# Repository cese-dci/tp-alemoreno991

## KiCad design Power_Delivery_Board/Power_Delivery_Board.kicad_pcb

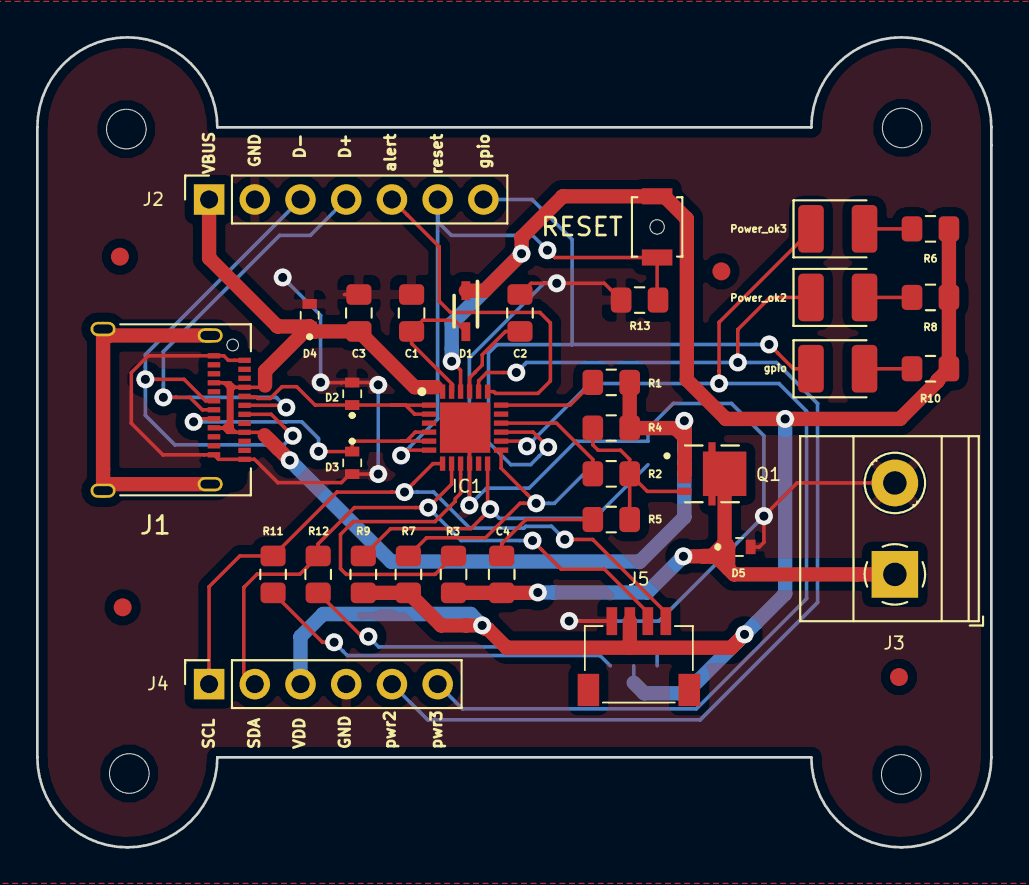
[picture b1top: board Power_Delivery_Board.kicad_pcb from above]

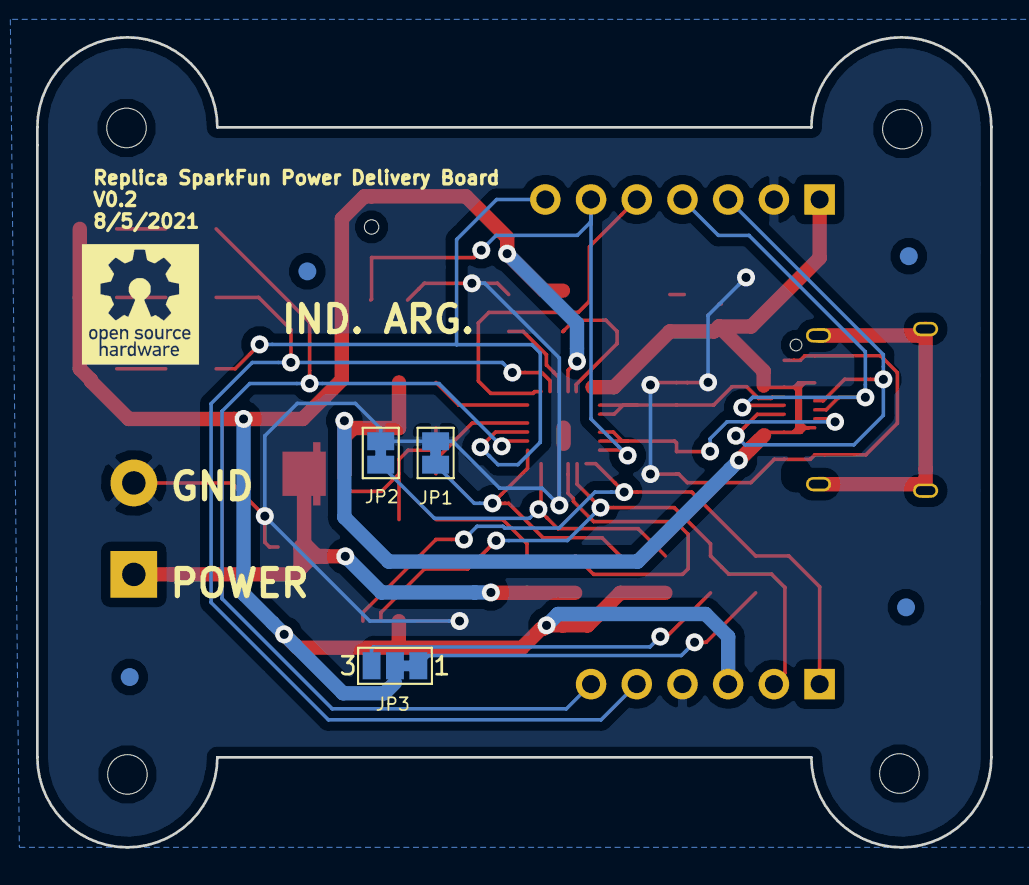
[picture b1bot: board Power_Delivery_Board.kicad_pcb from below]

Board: 2 copper layers, 53.0 x 45.0 mm, 36 parts (3 on the bottom side), 29 nets.

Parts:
C1, C2, C3: 1uF; C_0805_2012Metric_Pad1.15x1.40mm_HandSolder
C4: 0.1uF; C_0805_2012Metric_Pad1.15x1.40mm_HandSolder
D1: BAT60A; SOD2513X110N
D2, D3, D4, D5: 24V; ESDA8P801U1M
IC1: STUSB4500QTR; QFN50P400X400X100-25N-D
J1: USB C; USB_C_Receptacle_Amphenol_12401610E4-2A
J2: IO pins; PinSocket_1x07_P2.54mm_Vertical
J3: Power Output; TerminalBlock_Phoenix_MKDS-1,5-2-5.08_1x02_P5.08mm_Horizont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
J4: IO Pins; PinSocket_1x06_P2.54mm_Vertical
J5: Qwiic; 4208
JP1, JP2: solder_jumper; SolderJumper-2_P1.3mm_Bridged_Pad1.0x1.5mm
JP3: solder_jumper_triple; SolderJumper-3_P1.3mm_Bridged12_Pad1.0x1.5mm_NumberLabels
Power_ok2: amarillo; D_1210_3225Metric_Pad1.42x2.65mm_HandSolder
Power_ok3: azul; D_1210_3225Metric_Pad1.42x2.65mm_HandSolder
Q1: STL6P3LLH6; TRANS_STL6P3LLH6
R1, R3, R6, R8, R10: 1k; R_0805_2012Metric_Pad1.15x1.40mm_HandSolder
R2: 22k; R_0805_2012Metric_Pad1.15x1.40mm_HandSolder
R4, R7, R9, R13: 100k; R_0805_2012Metric_Pad1.15x1.40mm_HandSolder
R5: 100; R_0805_2012Metric_Pad1.15x1.40mm_HandSolder
R11, R12: 2k2; R_0805_2012Metric_Pad1.15x1.40mm_HandSolder
RESET: SW_Push; SW_SPST_B3U-1000P-B
gpio: verde; D_1210_3225Metric_Pad1.42x2.65mm_HandSolder

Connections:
/D+: J1.A6, J1.B6, J2.4
/D-: J1.A7, J1.B7, J2.3
/SCL: IC1.7, J4.1, J5.4, R11.2
/SDA: IC1.8, J4.2, J5.3, R12.2
/alert: IC1.19, J2.5
/cc1: D2.1, IC1.1, IC1.2, J1.A5
/cc2: D3.1, IC1.4, IC1.5, J1.B5
/gpio: IC1.15, J2.7, gpio.1
/power_ok2: IC1.20, J4.5, Power_ok2.1
/power_ok3: IC1.14, J4.6, Power_ok3.1
/reset: IC1.6, J2.6, R13.2, RESET.2
GND: C1.2, C2.2, C3.2, D2.2, D3.2, D4.2, D5.2, IC1.10, IC1.25, J1.A1, J1.A12, J1.B1, J1.B12, J2.2, J3.2, J4.4, J5.1, JP1.2, JP2.2, R13.1
unnamed: C1.1, D1.2, IC1.23
unnamed: C2.1, IC1.21
unnamed: C4.1, R5.1
unnamed: C4.2, D5.1, J3.1, Q1.5_8, R3.1
unnamed: Power_ok3.2, R6.2
unnamed: Power_ok2.2, R8.2
unnamed: R10.2, gpio.2
unnamed: IC1.9, R3.2
unnamed: IC1.12, JP2.1, R9.2
unnamed: IC1.13, JP1.1, R7.2
unnamed: IC1.16, R2.2
unnamed: IC1.18, R1.1
unnamed: JP3.1, R11.1
unnamed: JP3.3, R12.1
unnamed: Q1.4, R2.1, R4.1, R5.2
VBUS: C3.1, D4.1, IC1.24, J1.A4, J1.A9, J1.B4, J1.B9, J2.1, Q1.1, Q1.2, Q1.3, R1.2, R4.2
VDD: D1.1, IC1.22, J4.3, J5.2, JP3.2, R6.1, R7.1, R8.1, R9.1, R10.1, RESET.1

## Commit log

2021-03-31 Proyecto primera version (esquematico + pcb)
2021-03-31 agrego el .gitignore file
2021-03-31 ignorar archivos .zip
2021-04-02 Corrección de errores marcados por Fabiola
2021-04-02 Agrego un agujero para anclaje mecánico
2021-04-02 Revert "Intento de arreglar un problema en el esquematico"
    This reverts commit 567008187d0f758f3bd51b944ea173b35d1b1bc4.
2021-04-02 Agrego el modelo 3D del transistor faltante
2021-04-28 Correcciones Diego
2021-05-09 Correcciones finales
2021-05-10 Arreglo modelos 3d y borde PCB
2021-05-10 Arreglo borde PCB

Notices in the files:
Power_Delivery_Board/Power_Delivery_Board.kicad_pcb:
Released under the Creative Commons Attribution Share-Alike 4.0 Licence
